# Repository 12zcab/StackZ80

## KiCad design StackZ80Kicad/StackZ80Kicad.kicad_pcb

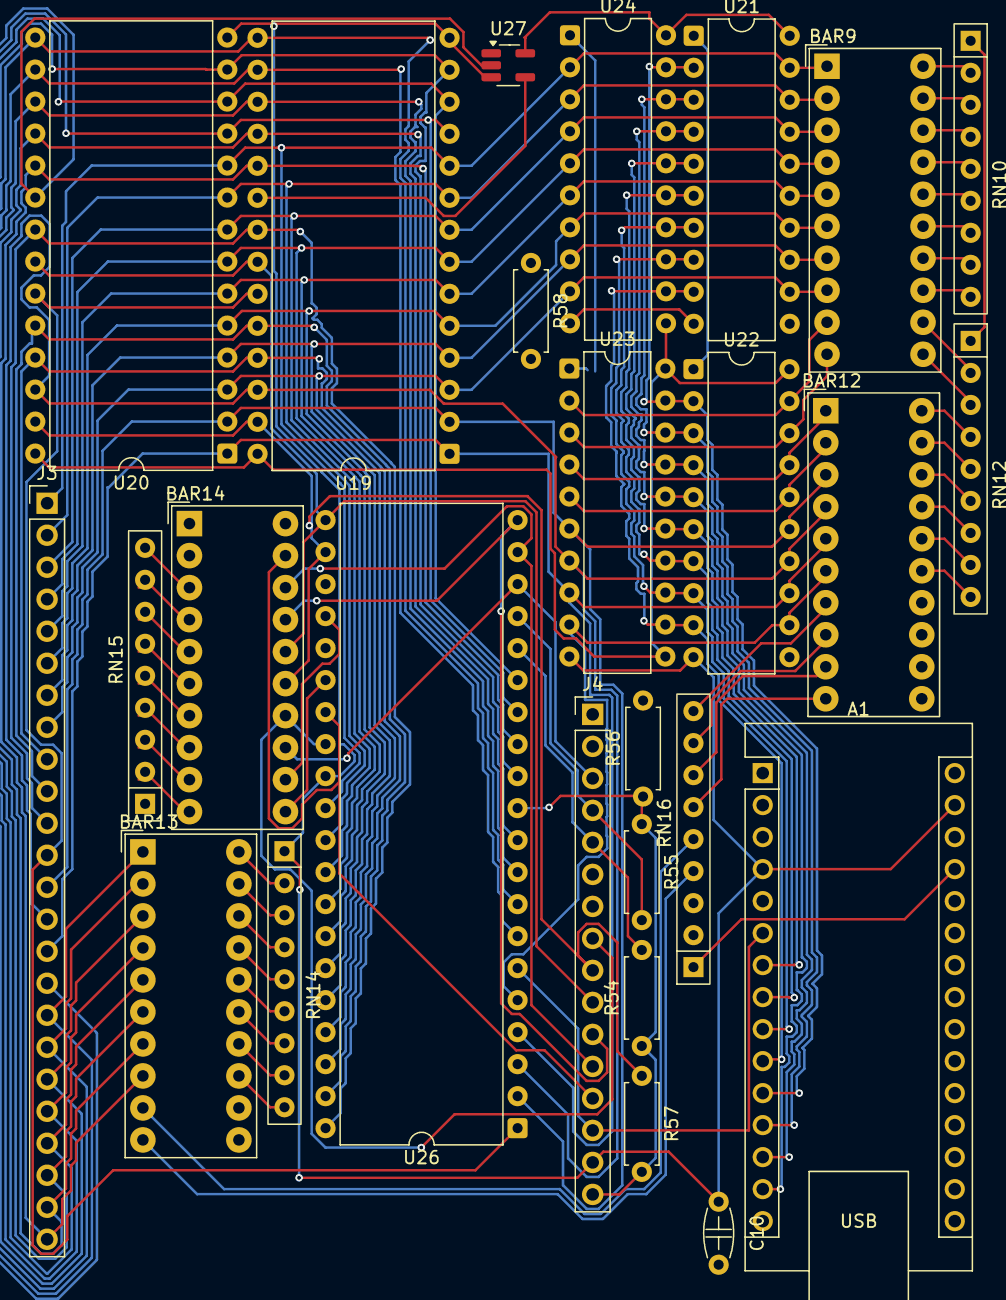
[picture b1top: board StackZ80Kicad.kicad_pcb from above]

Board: 2 copper layers, 26 parts (0 on the bottom side), 86 nets.

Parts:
A1: Arduino_Nano_v3.x; Arduino_Nano
BAR9, BAR12, BAR13, BAR14: HDSP-4830_2; HDSP-4830
C10: 104; C_Disc_D4.3mm_W1.9mm_P5.00mm
J3: Conn_01x24_Pin; PinHeader_1x24_P2.54mm_Vertical
J4: Conn_01x16_Pin; PinHeader_1x16_P2.54mm_Vertical
R54, R55, R56, R57, R58: 1k; R_Axial_DIN0207_L6.3mm_D2.5mm_P7.62mm_Horizontal
RN10, RN12, RN14, RN15, RN16: 1k_Resistor_Network; R_Array_SIP9
U19: CY62256-70PC; DIP-28_W15.24mm
U20: 28C256; DIP-28_W15.24mm
U21, U22, U23, U24: 74LS573; DIP-20_W7.62mm
U26: Z84C0010P; DIP-40_W15.24mm
U27: 74AHCT1G04; SOT-23-5_HandSoldering

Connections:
/Minimum Board/5V: A1.27 (+5V), C10.2, J4.16, R54.1, R55.1, R56.1, R57.2, R58.2, RN15.1 (common), RN16.1 (common), U19.28 (VCC), U20.28 (VCC), U21.20 (VCC), U22.20 (VCC), U23.11 (Load), U23.20 (VCC), U24.11 (Load), U24.20 (VCC), U26.11 (V_{CC}), U27.5 (VCC)
/Minimum Board/ADDR0: BAR9.1 (A), J3.1, U19.10 (A0), U20.10 (A0), U21.19 (Q0), U24.2 (D0), U26.30 (A_{0})
/Minimum Board/ADDR1: BAR9.2 (A), J3.2, U19.9 (A1), U20.9 (A1), U21.18 (Q1), U24.3 (D1), U26.31 (A_{1})
/Minimum Board/ADDR2: BAR9.3 (A), J3.3, U19.8 (A2), U20.8 (A2), U21.17 (Q2), U24.4 (D2), U26.32 (A_{2})
/Minimum Board/ADDR3: BAR9.4 (A), J3.4, U19.7 (A3), U20.7 (A3), U21.16 (Q3), U24.5 (D3), U26.33 (A_{3})
/Minimum Board/ADDR4: BAR9.5 (A), J3.5, U19.6 (A4), U20.6 (A4), U21.15 (Q4), U24.6 (D4), U26.34 (A_{4})
/Minimum Board/ADDR5: BAR9.6 (A), J3.6, U19.5 (A5), U20.5 (A5), U21.14 (Q5), U24.7 (D5), U26.35 (A_{5})
/Minimum Board/ADDR6: BAR9.7 (A), J3.7, U19.4 (A6), U20.4 (A6), U21.13 (Q6), U24.8 (D6), U26.36 (A_{6})
/Minimum Board/ADDR7: BAR9.8 (A), J3.8, U19.3 (A7), U20.3 (A7), U21.12 (Q7), U24.9 (D7), U26.37 (A_{7})
/Minimum Board/ADDR8: BAR9.9 (A), J3.9, U19.25 (A8), U20.25 (A8), U22.19 (Q0), U23.2 (D0), U26.38 (A_{8})
/Minimum Board/ADDR9: BAR9.10 (A), J3.10, U19.24 (A9), U20.24 (A9), U22.18 (Q1), U23.3 (D1), U26.39 (A_{9})
/Minimum Board/ADDR10: BAR12.1 (A), J3.11, U19.21 (A10), U20.21 (A10), U22.17 (Q2), U23.4 (D2), U26.40 (A_{10})
/Minimum Board/ADDR11: BAR12.2 (A), J3.12, U19.23 (A11), U20.23 (A11), U22.16 (Q3), U23.5 (D3), U26.1 (A_{11})
/Minimum Board/ADDR12: BAR12.3 (A), J3.13, U19.2 (A12), U20.2 (A12), U22.15 (Q4), U23.6 (D4), U26.2 (A_{12})
/Minimum Board/ADDR13: BAR12.4 (A), J3.14, U19.26 (A13), U20.26 (A13), U22.14 (Q5), U23.7 (D5), U26.3 (A_{13})
/Minimum Board/ADDR14: BAR12.5 (A), J3.15, U19.1 (A14), U20.1 (A14), U22.13 (Q6), U23.8 (D6), U26.4 (A_{14})
/Minimum Board/ADDR15: BAR12.6 (A), J3.16, U20.20 (~CS), U22.12 (Q7), U23.9 (D7), U26.5 (A_{15}), U27.2
/Minimum Board/CLK: A1.6 (D3), BAR14.20 (K), J4.14, U26.6 (CLK)
/Minimum Board/Data0: A1.11 (D8), BAR13.1 (A), J3.17, U19.11 (Q0), U20.11 (D0), U21.2 (D0), U22.2 (D0), U23.19 (Q0), U24.19 (Q0), U26.14 (D_{0})
/Minimum Board/Data1: A1.12 (D9), BAR13.2 (A), J3.18, U19.12 (Q1), U20.12 (D1), U21.3 (D1), U22.3 (D1), U23.18 (Q1), U24.18 (Q1), U26.15 (D_{1})
/Minimum Board/Data2: A1.13 (D10), BAR13.3 (A), J3.19, U19.13 (Q2), U20.13 (D2), U21.4 (D2), U22.4 (D2), U23.17 (Q2), U24.17 (Q2), U26.12 (D_{2})
/Minimum Board/Data3: A1.14 (D11), BAR13.4 (A), J3.20, U19.15 (Q3), U20.15 (D3), U21.5 (D3), U22.5 (D3), U23.16 (Q3), U24.16 (Q3), U26.8 (D_{3})
/Minimum Board/Data4: A1.7 (D4), BAR13.5 (A), J3.21, U19.16 (Q4), U20.16 (D4), U21.6 (D4), U22.6 (D4), U23.15 (Q4), U24.15 (Q4), U26.7 (D_{4})
/Minimum Board/Data5: A1.8 (D5), BAR13.6 (A), J3.22, U19.17 (Q5), U20.17 (D5), U21.7 (D5), U22.7 (D5), U23.14 (Q5), U24.14 (Q5), U26.9 (D_{5})
/Minimum Board/Data6: A1.9 (D6), BAR13.7 (A), J3.23, U19.18 (Q6), U20.18 (D6), U21.8 (D6), U22.8 (D6), U23.13 (Q6), U24.13 (Q6), U26.10 (D_{6})
/Minimum Board/Data7: A1.10 (D7), BAR13.8 (A), J3.24, U19.19 (Q7), U20.19 (D7), U21.9 (D7), U22.9 (D7), U23.12 (Q7), U24.12 (Q7), U26.13 (D_{7})
/Minimum Board/GND: A1.4 (GND), A1.29 (GND), C10.1, J4.15, RN10.1 (common), RN12.1 (common), RN14.1 (common), U19.14 (GND), U20.14 (GND), U21.10 (GND), U22.10 (GND), U23.10 (GND), U24.10 (GND), U26.29 (GND), U27.3 (GND)
/Minimum Board/Load_O_1: A1.24 (A5), U21.11 (Load)
/Minimum Board/Load_O_2: A1.23 (A4), U22.11 (Load)
/Minimum Board/OE_I1: A1.26 (A7), U24.1 (OE)
/Minimum Board/OE_I2: A1.25 (A6), U23.1 (OE)
/Minimum Board/OE_O: A1.5 (D2), U21.1 (OE), U22.1 (OE)
/Minimum Board/~BUSACK: BAR12.13 (K), J4.6, U26.23 (~BUSACK)
/Minimum Board/~BUSREQ: A1.19 (A0), BAR12.14 (K), J4.7, U26.25 (~BUSREQ)
/Minimum Board/~HALT: A1.16 (D13), BAR14.13 (K), J4.3, U26.18 (~HALT)
/Minimum Board/~INT: BAR12.12 (K), J4.5, R54.2, U26.16 (~INT)
/Minimum Board/~IORQ: A1.15 (D12), BAR14.17 (K), J4.11, U26.20 (~IORQ)
/Minimum Board/~M1: BAR14.19 (K), J4.13, U26.27 (~M1)
/Minimum Board/~MREQ: BAR14.18 (K), J4.12, U26.19 (~MREQ)
/Minimum Board/~NMI: BAR12.11 (K), J4.4, R55.2, U26.17 (~NMI)
/Minimum Board/~RD: A1.22 (A3), BAR14.16 (K), J4.10, R58.1, U19.22 (~OE), U20.22 (~OE), U26.21 (~RD)
/Minimum Board/~RESET: A1.20 (A1), BAR14.11 (K), J4.1, U26.26 (~RESET)
/Minimum Board/~RFSH: BAR14.14 (K), J4.8, U26.28 (~RFSH)
/Minimum Board/~WAIT: BAR14.12 (K), J4.2, R56.2, U26.24 (~WAIT)
/Minimum Board/~WR: A1.21 (A2), BAR14.15 (K), J4.9, R57.1, U19.27 (~WE), U20.27 (~WE), U26.22 (~WR)
unnamed: BAR9.20 (K), RN10.2 (R1)
unnamed: BAR9.19 (K), RN10.3 (R2)
unnamed: BAR9.18 (K), RN10.4 (R3)
unnamed: BAR9.17 (K), RN10.5 (R4)
unnamed: BAR9.16 (K), RN10.6 (R5)
unnamed: BAR9.15 (K), RN10.7 (R6)
unnamed: BAR9.14 (K), RN10.8 (R7)
unnamed: BAR9.13 (K), RN10.9 (R8)
unnamed: BAR9.12 (K), RN12.2 (R1)
unnamed: BAR9.11 (K), RN12.3 (R2)
unnamed: BAR12.20 (K), RN12.4 (R3)
unnamed: BAR12.19 (K), RN12.5 (R4)
unnamed: BAR12.18 (K), RN12.6 (R5)
unnamed: BAR12.17 (K), RN12.7 (R6)
unnamed: BAR12.16 (K), RN12.8 (R7)
unnamed: BAR12.15 (K), RN12.9 (R8)
unnamed: BAR13.20 (K), RN14.2 (R1)
unnamed: BAR13.19 (K), RN14.3 (R2)
unnamed: BAR13.18 (K), RN14.4 (R3)
unnamed: BAR13.17 (K), RN14.5 (R4)
unnamed: BAR13.16 (K), RN14.6 (R5)
unnamed: BAR13.15 (K), RN14.7 (R6)
unnamed: BAR13.14 (K), RN14.8 (R7)
unnamed: BAR13.13 (K), RN14.9 (R8)
unnamed: BAR14.10 (A), RN15.2 (R1)
unnamed: BAR14.9 (A), RN15.3 (R2)
unnamed: BAR14.8 (A), RN15.4 (R3)
unnamed: BAR14.7 (A), RN15.5 (R4)
unnamed: BAR14.6 (A), RN15.6 (R5)
unnamed: BAR14.5 (A), RN15.7 (R6)
unnamed: BAR14.4 (A), RN15.8 (R7)
unnamed: BAR14.3 (A), RN15.9 (R8)
unnamed: BAR14.2 (A), RN16.2 (R1)
unnamed: BAR14.1 (A), RN16.3 (R2)
unnamed: BAR13.10 (A), RN16.4 (R3)
unnamed: BAR13.9 (A), RN16.5 (R4)
unnamed: BAR12.10 (A), RN16.6 (R5)
unnamed: BAR12.9 (A), RN16.7 (R6)
unnamed: BAR12.8 (A), RN16.8 (R7)
unnamed: BAR12.7 (A), RN16.9 (R8)
unnamed: U19.20 (~CS), U27.4
